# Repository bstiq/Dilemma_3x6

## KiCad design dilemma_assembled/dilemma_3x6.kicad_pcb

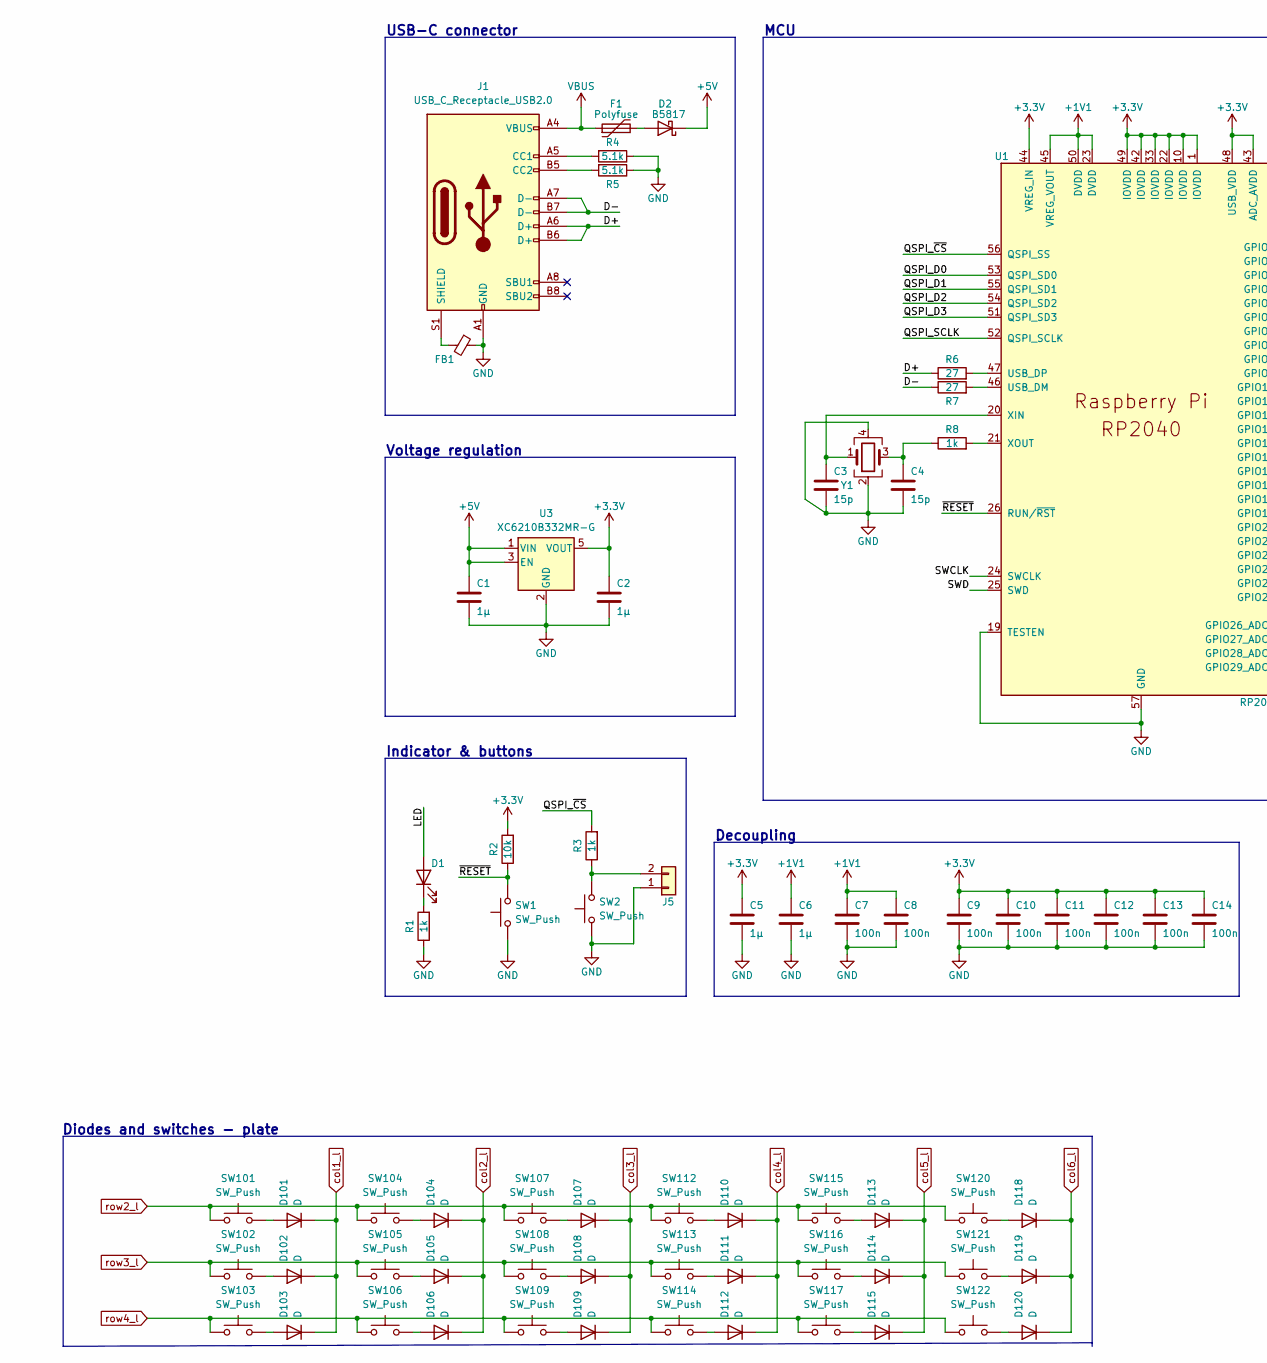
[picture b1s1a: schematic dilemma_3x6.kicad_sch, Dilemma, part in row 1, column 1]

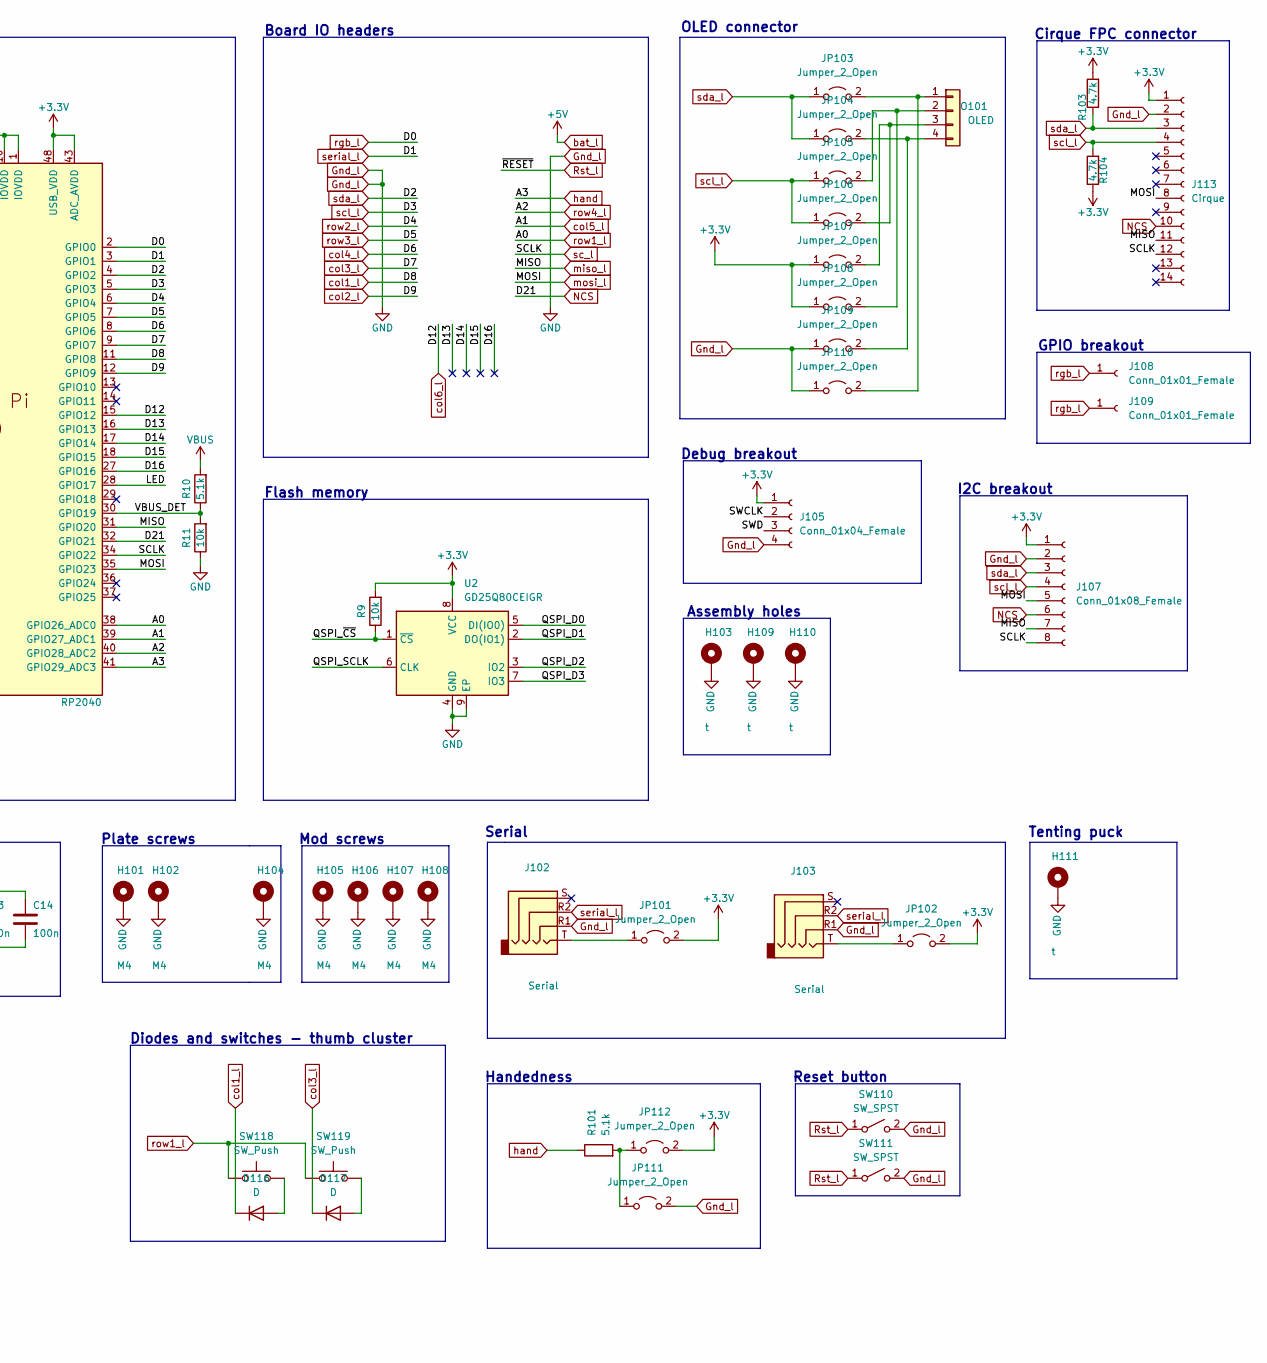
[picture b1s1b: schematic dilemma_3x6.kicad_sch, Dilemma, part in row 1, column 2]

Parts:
C1, C2: 1µ; C_0603_1608Metric; LCSC C19666
C3, C4: 15p; C_0402_1005Metric; LCSC C1548
C5, C6: 1µ; C_0402_1005Metric; LCSC C52923
C7, C8, C9, C10, C11, C12, C13, C14: 100n; C_0402_1005Metric; LCSC C1525
D1: LED; LED_0402_1005Metric; LCSC C130719
D2: B5817; D_SOD-323; LCSC C123899
D101, D102, D103, D104, D105, D106, D107, D108, D109, D110, D111, D112, D113, D114, D115, D116, D117, D118, D119, D120: D; D_1206_handsolder_reversible
F1: Polyfuse; Fuse_0603_1608Metric; LCSC C69679
FB1: FerriteBead_Small; L_0603_1608Metric; LCSC C98288
H101, H102, H104, H105, H106, H107, H108: M4; MountingHole_3mm_Pad_Via
H103, H109, H110: t; JLC_SMT_Assembly_Hole
H111: t; Tenting_Puck
J1: USB_C_Receptacle_USB2.0; USB_C_Receptacle_HRO_TYPE-C-31-M-13B; LCSC C2848619
J5: Conn_01x02; PinHeader_1x02_P1.27mm_Vertical
J102, J103: Serial; Jack_3.5mm_PJ320E_Horizontal_custom
J105: Conn_01x04_Female; PinHeader_1x04_P2.54mm_Vertical_debug
J107: Conn_01x08_Female; 1x08 smd reversible
J108, J109: Conn_01x01_Female; SolderWirePad_1x01_SMD_1x2mm
J113: Cirque; FPC-SMD_FPC05012-09200-.5mm
JP101, JP102, JP103, JP104, JP105, JP106, JP107, JP108, JP109, JP110, JP111, JP112: Jumper_2_Open; SolderJumper-2_P1.3mm_Open_RoundedPad1.0x1.5mm
O101: OLED; PinHeader_1x04_P2.54mm_Vertical
R1, R3, R8: 1k; R_0402_1005Metric; LCSC C11702
R2, R9, R11: 10k; R_0402_1005Metric; LCSC C25744
R4, R5, R10: 5.1k; R_0402_1005Metric; LCSC C25905
R6, R7: 27; R_0402_1005Metric; LCSC C25100
R101: 5.1k; R_0402_1005Metric_nolabel; JLCPCB BOM 1
R103, R104: 4.7k; R_0402_1005Metric_nolabel; LCSC C269746
SW1, SW2: SW_Push; SW_SPST_CK_KXT3; LCSC C319433
SW101, SW102, SW103, SW104, SW105, SW106, SW107, SW108, SW109, SW112, SW113, SW114, SW115, SW116, SW117, SW118, SW119, SW120, SW121, SW122: SW_Push; SW_MX_choc
SW110, SW111: SW_SPST; SW_Push_1P1T_NO_6x6mm_H9.5mm
U1: RP2040; QFN-56-1EP_7x7mm_P0.4mm_EP3.2x3.2mm; LCSC C2040
U2: GD25Q80CEIGR; USON-8-1EP_3x2mm_P0.5mm_EP0.25x1.65mm; LCSC C395484
U3: XC6210B332MR-G; SOT-23-5; LCSC C82942
Y1: Crystal_GND24; Crystal_SMD_2520-4Pin_2.5x2.0mm; LCSC C2149204

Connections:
+1V1: C6.1, C7.1, C8.1, U1.23 (DVDD), U1.45 (VREG_VOUT), U1.50 (DVDD)
+3V3: C2.1, C5.1, C9.1, C10.1, C11.1, C12.1, C13.1, C14.1, J105.1, J107.1, J113.1, JP101.2 (B), JP102.2 (B), JP107.1 (A), JP108.1 (A), JP112.2 (B), R2.2, R9.2, R103.2, R104.1, U1.1 (IOVDD), U1.10 (IOVDD), U1.22 (IOVDD), U1.33 (IOVDD), U1.42 (IOVDD), U1.43 (ADC_AVDD), U1.44 (VREG_IN), U1.48 (USB_VDD), U1.49 (IOVDD), U2.8 (VCC), U3.5 (VOUT)
/D13: U1.16 (GPIO13)
/D14: U1.17 (GPIO14)
/D15: U1.18 (GPIO15)
/D16: U1.27 (GPIO16)
/D+: J1.A6 (D+), J1.B6 (D+), R6.1
/D-: J1.A7 (D-), J1.B7 (D-), R7.1
/LED: D1.2 (A), U1.28 (GPIO17)
/QSPI_D0: U1.53 (QSPI_SD0), U2.5 (DI(IO0))
/QSPI_D1: U1.55 (QSPI_SD1), U2.2 (DO(IO1))
/QSPI_D2: U1.54 (QSPI_SD2), U2.3 (IO2)
/QSPI_D3: U1.51 (QSPI_SD3), U2.7 (IO3)
/QSPI_SCLK: U1.52 (QSPI_SCLK), U2.6 (CLK)
/QSPI_~CS: R3.2, R9.1, U1.56 (QSPI_SS), U2.1 (~CS)
/SWCLK: J105.2, U1.24 (SWCLK)
/SWD: J105.3, U1.25 (SWD)
/VBUS_DET: R10.1, R11.2, U1.30 (GPIO19)
Gnd_l: C1.2, C2.2, C3.2, C4.2, C5.2, C6.2, C7.2, C8.2, C9.2, C10.2, C11.2, C12.2, C13.2, C14.2, FB1.1, H101.1, H102.1, H103.1, H104.1, H105.1, H106.1, H107.1, H108.1, H109.1, H110.1, H111.1, J1.A1 (GND), J1.A12 (GND), J1.B1 (GND), J1.B12 (GND), J5.1, J102.R1, J103.R1, J105.4, J107.2, J113.2, JP109.1 (A), JP110.1 (A), JP111.2 (B), R1.1, R4.1, R5.1, R11.1, SW1.1, SW2.1, SW110.2 (B), SW111.2 (B), U1.19 (TESTEN), U1.57 (GND), U2.4 (GND), U2.9 (EP), U3.2 (GND), Y1.2, Y1.4
NCS: J107.6, J113.10, U1.32 (GPIO21)
unnamed: C3.1, U1.20 (XIN), Y1.1
unnamed: C4.1, R8.1, Y1.3
unnamed: D1.1 (K), R1.2
unnamed: D2.2 (A), F1.2
unnamed: D101.2 (A), SW101.2
unnamed: D102.2 (A), SW102.2
unnamed: D103.2 (A), SW103.2
unnamed: D104.2 (A), SW104.2
unnamed: D105.2 (A), SW105.2
unnamed: D106.2 (A), SW106.2
unnamed: D107.2 (A), SW107.2
unnamed: D108.2 (A), SW108.2
unnamed: D109.2 (A), SW109.2
unnamed: D110.2 (A), SW112.2
unnamed: D111.2 (A), SW113.2
unnamed: D112.2 (A), SW114.2
unnamed: D113.2 (A), SW115.2
unnamed: D114.2 (A), SW116.2
unnamed: D115.2 (A), SW117.2
unnamed: D116.2 (A), SW118.2
unnamed: D117.2 (A), SW119.2
unnamed: D118.2 (A), SW120.2
unnamed: D119.2 (A), SW121.2
unnamed: D120.2 (A), SW122.2
unnamed: FB1.2, J1.S1 (SHIELD)
unnamed: J1.A5 (CC1), R4.2
unnamed: J1.B5 (CC2), R5.2
unnamed: J5.2, R3.1, SW2.2
unnamed: J102.T, JP101.1 (A)
unnamed: J103.T, JP102.1 (A)
unnamed: JP103.2 (B), JP110.2 (B), O101.1
unnamed: JP104.2 (B), JP109.2 (B), O101.4
unnamed: JP105.2 (B), JP108.2 (B), O101.2
unnamed: JP106.2 (B), JP107.2 (B), O101.3
unnamed: JP111.1 (A), JP112.1 (A), R101.2
unnamed: R6.2, U1.47 (USB_DP)
unnamed: R7.2, U1.46 (USB_DM)
unnamed: R8.2, U1.21 (XOUT)
Rst_l: R2.1, SW1.2, SW110.1 (A), SW111.1 (A), U1.26 (RUN/~RST)
VBUS: F1.1, J1.A4 (VBUS), J1.A9 (VBUS), J1.B4 (VBUS), J1.B9 (VBUS), R10.2
bat_l: C1.1, D2.1 (K), U3.1 (VIN), U3.3 (EN)
col1_l: D101.1 (K), D102.1 (K), D103.1 (K), D116.1 (K), U1.11 (GPIO8)
col2_l: D104.1 (K), D105.1 (K), D106.1 (K), U1.12 (GPIO9)
col3_l: D107.1 (K), D108.1 (K), D109.1 (K), D117.1 (K), U1.9 (GPIO7)
col4_l: D110.1 (K), D111.1 (K), D112.1 (K), U1.8 (GPIO6)
col5_l: D113.1 (K), D114.1 (K), D115.1 (K), U1.39 (GPIO27_ADC1)
col6_l: D118.1 (K), D119.1 (K), D120.1 (K), U1.15 (GPIO12)
hand: R101.1, U1.41 (GPIO29_ADC3)
miso_l: J107.7, J113.11, U1.31 (GPIO20)
mosi_l: J107.5, J113.8, U1.35 (GPIO23)
rgb_l: J108.1, J109.1, U1.2 (GPIO0)
row1_l: SW118.1, SW119.1, U1.38 (GPIO26_ADC0)
row2_l: SW101.1, SW104.1, SW107.1, SW112.1, SW115.1, SW120.1, U1.6 (GPIO4)
row3_l: SW102.1, SW105.1, SW108.1, SW113.1, SW116.1, SW121.1, U1.7 (GPIO5)
row4_l: SW103.1, SW106.1, SW109.1, SW114.1, SW117.1, SW122.1, U1.40 (GPIO28_ADC2)
sc_l: J107.8, J113.12, U1.34 (GPIO22)
scl_l: J107.4, J113.4, JP105.1 (A), JP106.1 (A), R104.2, U1.5 (GPIO3)
sda_l: J107.3, J113.3, JP103.1 (A), JP104.1 (A), R103.1, U1.4 (GPIO2)
serial_l: J102.R2, J103.R2, U1.3 (GPIO1)

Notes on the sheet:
Tenting puck
Debug breakout
Decoupling
Board IO headers
USB-C connector
Reset button
I2C breakout
Diodes and switches - plate
Cirque FPC connector
Mod screws
Indicator & buttons
Voltage regulation
Handedness
Assembly holes
Serial
Plate screws
OLED connector
MCU
Diodes and switches - thumb cluster
GPIO breakout
Flash memory

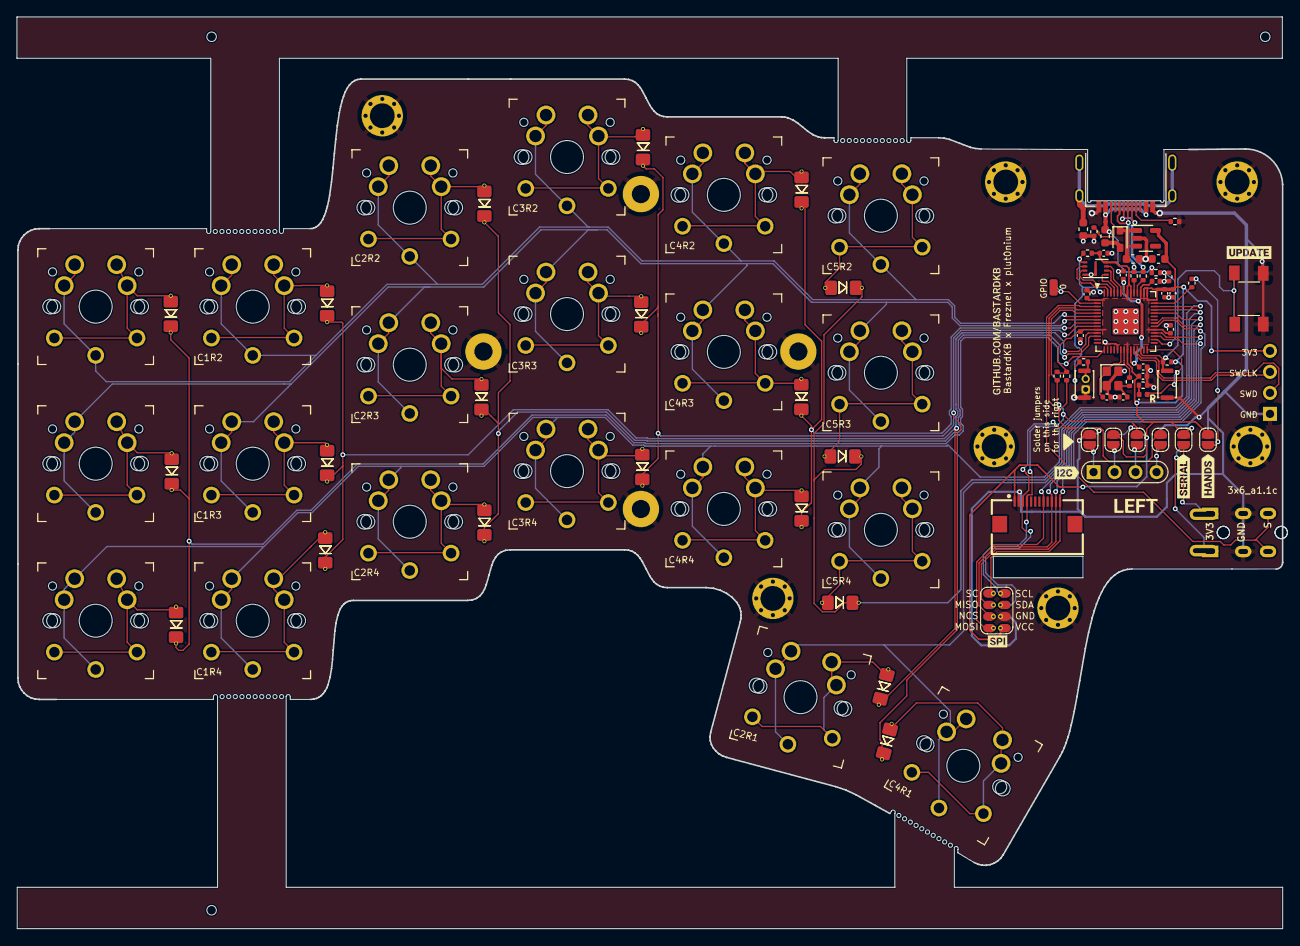
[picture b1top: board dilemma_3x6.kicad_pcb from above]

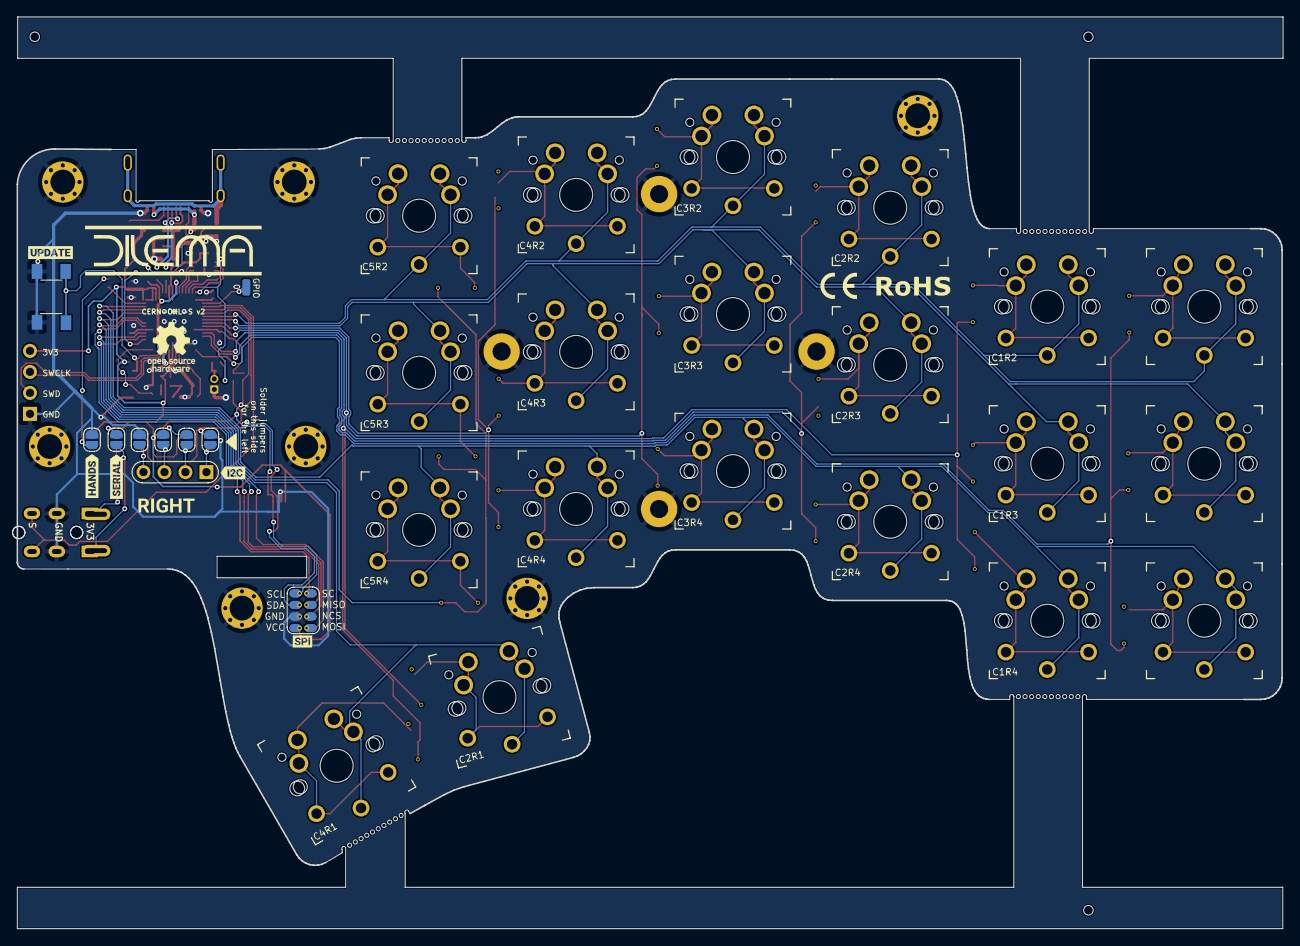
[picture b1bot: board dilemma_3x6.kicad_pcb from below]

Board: 2 copper layers, 153.1 x 110.3 mm, 126 parts (15 on the bottom side), 75 nets.

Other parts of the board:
kibuzzard-61F01A92: G***; kibuzzard-61F01A92
kibuzzard-62C1A775, kibuzzard-62C1A775#2: G***; kibuzzard-62C1A775
kibuzzard-62C19A64, kibuzzard-62C19A64#2: G***; kibuzzard-62C19A64
kibuzzard-62C19AB4: G***; kibuzzard-62C19AB4
kibuzzard-62C19AC2: G***; kibuzzard-62C19AC2
kibuzzard-62C19AE7, kibuzzard-62C19AE7#2: G***; kibuzzard-62C19AE7
kibuzzard-62C55DF6, kibuzzard-62C55DF6#2: G***; kibuzzard-62C55DF6
kibuzzard-62C547B3: G***; kibuzzard-62C547B3
kibuzzard-62C5480E: G***; kibuzzard-62C5480E

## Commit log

2022-08-31 add 6th column
2022-08-31 annotate schematic
2022-09-01 update file names
2022-09-02 update bom
2022-09-05 add back puck
2022-09-06 fix R103 R104 bom

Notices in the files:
dilemma_assembled/dilemma_3x6.kicad_pcb:
CERN-OHL-S v2
dilemma_assembled/dilemma_3x6.kicad_sch:
Licensed under CERN-OHL-W v2
